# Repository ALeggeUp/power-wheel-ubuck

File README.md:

# Power Wheel &#956;Buck

This project is a synchronous buck converter providing 5V at 3A from 4.5-V to 17-V input.

# License

This work is licensed under the Creative Commons Attribution 4.0 International License. To view a copy of this license, visit http://creativecommons.org/licenses/by/4.0/ or send a letter to Creative Commons, PO Box 1866, Mountain View, CA 94042, USA.

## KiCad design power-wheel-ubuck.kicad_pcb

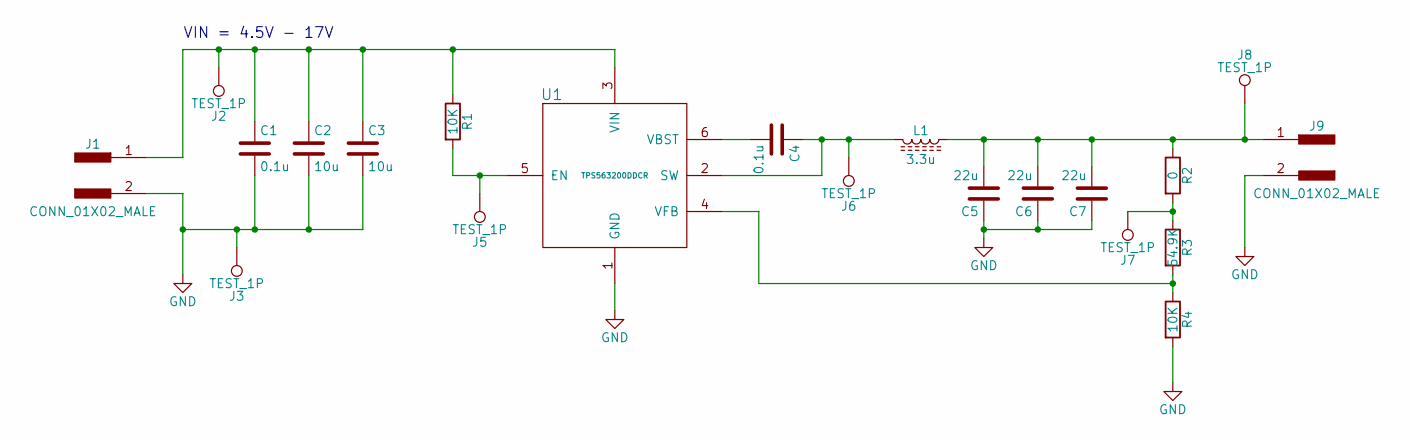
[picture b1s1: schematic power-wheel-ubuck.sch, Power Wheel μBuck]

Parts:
C1, C4: 0.1u; C_0805_HandSoldering; MPN CC0805KRX7R9BB104
C2, C3: 10u; C_0805_HandSoldering; MPN GRM21BR61E106KA73L
C5, C6, C7: 22u; C_0805_HandSoldering; MPN CL21A226MOCLRNC
J1, J9: CONN_01X02_MALE; Pin_Header_Straight_1x02_Pitch2.54mm
J2, J3, J5, J6, J7, J8: TEST_1P; Measurement_Point_Square-SMD-Pad_Small
L1: 3.3u; VLS5045EX
R1, R4: 10K; R_0805_HandSoldering
R2: 0; R_0805_HandSoldering
R3: 54.9K; R_0805_HandSoldering
U1: TPS563200DDCR; SOT-23-6_Handsoldering; MPN TPS563200DDCR

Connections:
GND: C1.2, C2.2, C3.2, C5.1, C6.1, C7.1, J1.2, J3.1, J9.2, R4.2, U1.1 (GND)
unnamed: C1.1, C2.1, C3.1, J1.1, J2.1, R1.1, U1.3 (VIN)
unnamed: C4.1, J6.1, L1.2, U1.2 (SW)
unnamed: C4.2, U1.6 (VBST)
unnamed: C5.2, C6.2, C7.2, J8.1, J9.1, L1.1, R2.1
unnamed: J5.1, R1.2, U1.5 (EN)
unnamed: J7.1, R2.2, R3.1
unnamed: R3.2, R4.1, U1.4 (VFB)

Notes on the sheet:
VIN = 4.5V - 17V

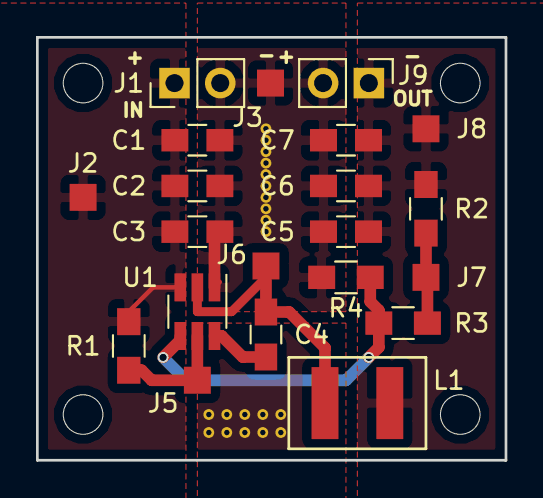
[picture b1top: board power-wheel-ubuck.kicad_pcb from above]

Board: 2 copper layers, 26.0 x 23.5 mm, 21 parts (0 on the bottom side), 8 nets.

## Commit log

2017-06-18 Initial commit with simple readme and license
2017-06-18 Initial Kicad project files
2017-06-18 TPS56x200 datasheet
2017-06-18 TPS563200EVM-652 evaluation module documentation for reference
2017-06-18 BOM created by TI WEBENCH Designer
2017-06-18 Datasheet for potential 3.3uH inductor
2017-06-18 Add new TPS563200DDCR symbol and add library to the project
2017-06-18 Add properties to schematic page and change page size
2017-06-18 Added initial symbol to schematic
2017-06-18 Moved pins around in symbols for easier wiring
2017-06-18 Schematic captured for initial run at board based on the TPS563200EVM-652 eval board
2017-06-19 Annotated parts and assigned values
2017-06-19 VLS5045EX inductor footprint in passives module
2017-06-19 Associated footprints with parts
2017-06-19 Added all footprints to the board to start layout
2017-06-19 Remove redundant testpoint
2017-06-19 Initial layout start
2017-06-19 First attempt at layout, needs tightening up
2017-06-20 Smaller test pad points
2017-06-20 Created VIA footprint and added it to the project
2017-06-20 Remove 1x03 pin header
2017-06-20 Removed the "jumper switch" and moved things in to fill the hole
2017-06-20 Tightened up the layout
2017-06-20 Add part numbers and links to the capacitors
2017-06-20 Add some text on the back of the board
2017-06-20 Add some in and out indicators
2017-06-20 Add a 3D screenshot to the README
